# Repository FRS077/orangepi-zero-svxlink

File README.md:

# Shield OrangePi zero SvxLink

The purpose of this PCB is to easily interface one or two radio transceivers with an Orange Pi Zero. This makes it easy to create a simplex or duplex SvxLink access point.

It is assembled on top of the Orange Pi Zero and connected to the radios by two mini DIN connectors.

## Built With

- KiCad v7 - _Open Source CAD software_
- KiCad v7 Librairies - _Symbols, footprints and 3D models librairies_
- LCSC - _Electronic parts provider_ & JLCPCB - _Board manufacturing_

## Specifications

### Mini DIN Pinout

| No Pin | Simplex / Duplex RX | Duplex TX |
| :----: | :-----------------: | :-------: |
|   1    |      Audio Out      | Audio Out |
|   2    |       Ground        |  Ground   |
|   3    |         PTT         |    PTT    |
|   4    |   Audio In (9600)   |   _N/C_   |
|   5    |   Audio In (1200)   |   _N/C_   |
|   6    |       Squelch       |   _N/C_   |

PTT is connected on the Orange Pi Zero to PA07 and Squelch to PA10.

### Solder bridge selectors

| Name  | Usage                                     |         Choice A          |   Choice B    |
| :---: | :---------------------------------------- | :-----------------------: | :-----------: |
|  JP1  | Select the audio input                    | Audio In 1200 _(default)_ | Audio In 9600 |
|  JP2  | Select simplex/duplex mode (audio output) |        Duplex mode        |  Simplex mode |
|  JP3  | Select simplex/duplex mode (PTT)          |        Duplex mode        |  Simplex mode |

## Authors

- **Quentin Rahms** - _Intial work_
- **Alexis Moyart** - _Completion_

## License

This project is licensed under the MIT License - see the LICENSE.md file for details

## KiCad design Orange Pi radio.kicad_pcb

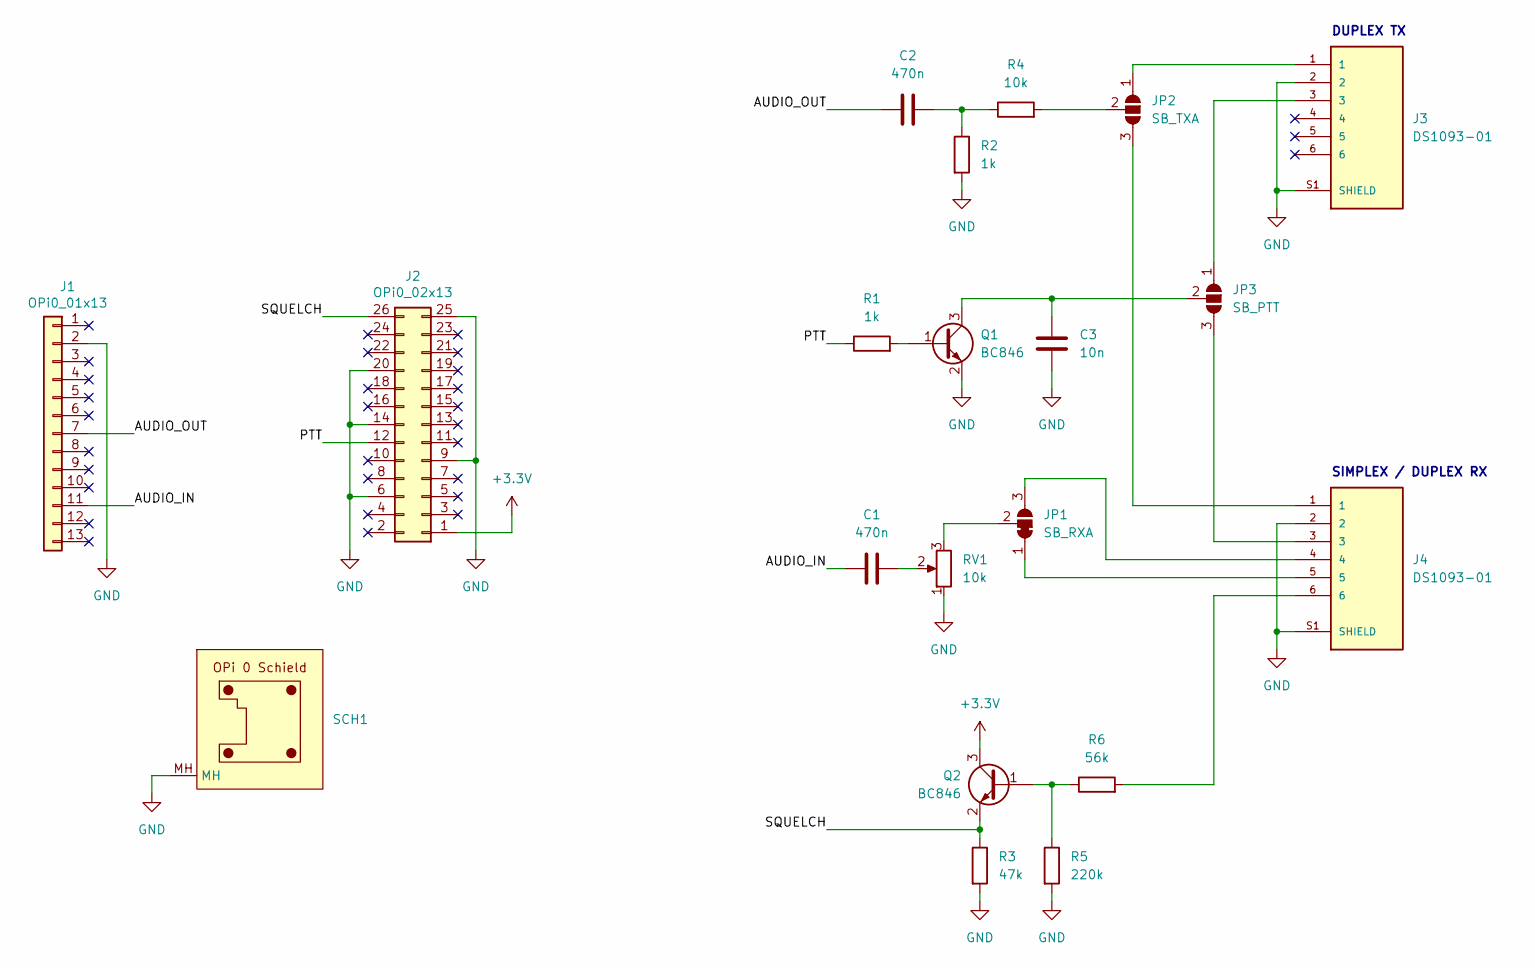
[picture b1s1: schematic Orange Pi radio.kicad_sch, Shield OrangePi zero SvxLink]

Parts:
C1, C2: 470n; C_0603_1608Metric_Pad1.08x0.95mm_HandSolder
C3: 10n; C_0603_1608Metric_Pad1.08x0.95mm_HandSolder
J1: OPi0_01x13; PinSocket_1x13_P2.54mm_Vertical
J2: OPi0_02x13; PinSocket_2x13_P2.54mm_Vertical
J3, J4: DS1093-01
JP1: SB_RXA; SolderJumper-3_P1.3mm_Bridged12_RoundedPad1.0x1.5mm
JP2: SB_TXA; SolderJumper-3_P1.3mm_Open_RoundedPad1.0x1.5mm
JP3: SB_PTT; SolderJumper-3_P1.3mm_Open_RoundedPad1.0x1.5mm
Q1, Q2: BC846; SOT-23
R1, R2: 1k; R_0603_1608Metric_Pad0.98x0.95mm_HandSolder
R3: 47k; R_0603_1608Metric_Pad0.98x0.95mm_HandSolder
R4: 10k; R_0603_1608Metric_Pad0.98x0.95mm_HandSolder
R5: 220k; R_0603_1608Metric_Pad0.98x0.95mm_HandSolder
R6: 56k; R_0603_1608Metric_Pad0.98x0.95mm_HandSolder
RV1: 10k; Potentiometer_Bourns_3314G_Vertical
SCH1: OPi0_schield

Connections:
+3.3V: J2.1, Q2.3 (C)
/AUDIO_IN: C1.1, J1.11
/AUDIO_OUT: C2.1, J1.7
/PTT: J2.12, R1.1
/SQUELCH: J2.26, Q2.2 (E), R3.1
GND: C3.2, J1.2, J2.6, J2.9, J2.14, J2.20, J2.25, J3.2, J3.S1 (SHIELD), J3.S2 (SHIELD), J3.S3 (SHIELD), J4.2, J4.S1 (SHIELD), J4.S2 (SHIELD), J4.S3 (SHIELD), Q1.2 (E), R2.2, R3.2, R5.2, RV1.1, SCH1.MH
unnamed: C1.2, RV1.2
unnamed: C2.2, R2.1, R4.1
unnamed: J4.6, R6.2
unnamed: J4.5, JP1.1 (A)
unnamed: J4.4, JP1.3 (B)
unnamed: JP1.2 (C), RV1.3
unnamed: J3.1, JP2.1 (A)
unnamed: J4.1, JP2.3 (B)
unnamed: JP2.2 (C), R4.2
unnamed: J3.3, JP3.1 (A)
unnamed: J4.3, JP3.3 (B)
unnamed: C3.1, JP3.2 (C), Q1.3 (C)
unnamed: Q1.1 (B), R1.2
unnamed: Q2.1 (B), R5.1, R6.1

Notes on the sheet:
SIMPLEX / DUPLEX RX
DUPLEX TX

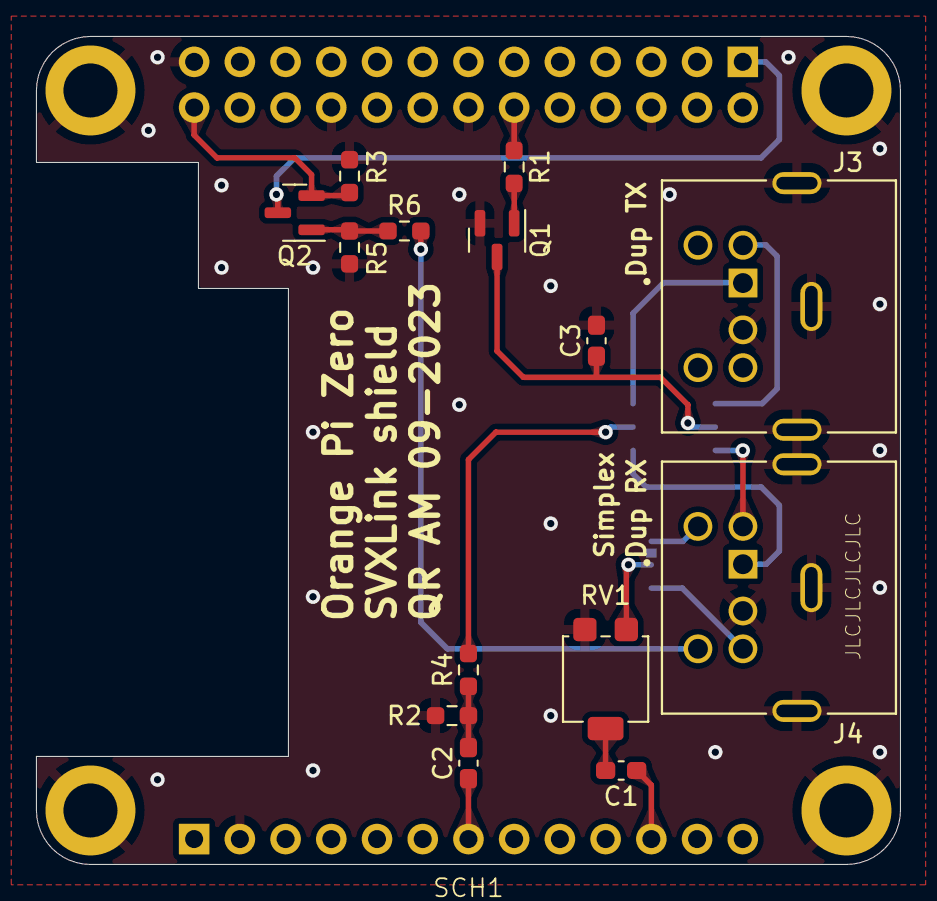
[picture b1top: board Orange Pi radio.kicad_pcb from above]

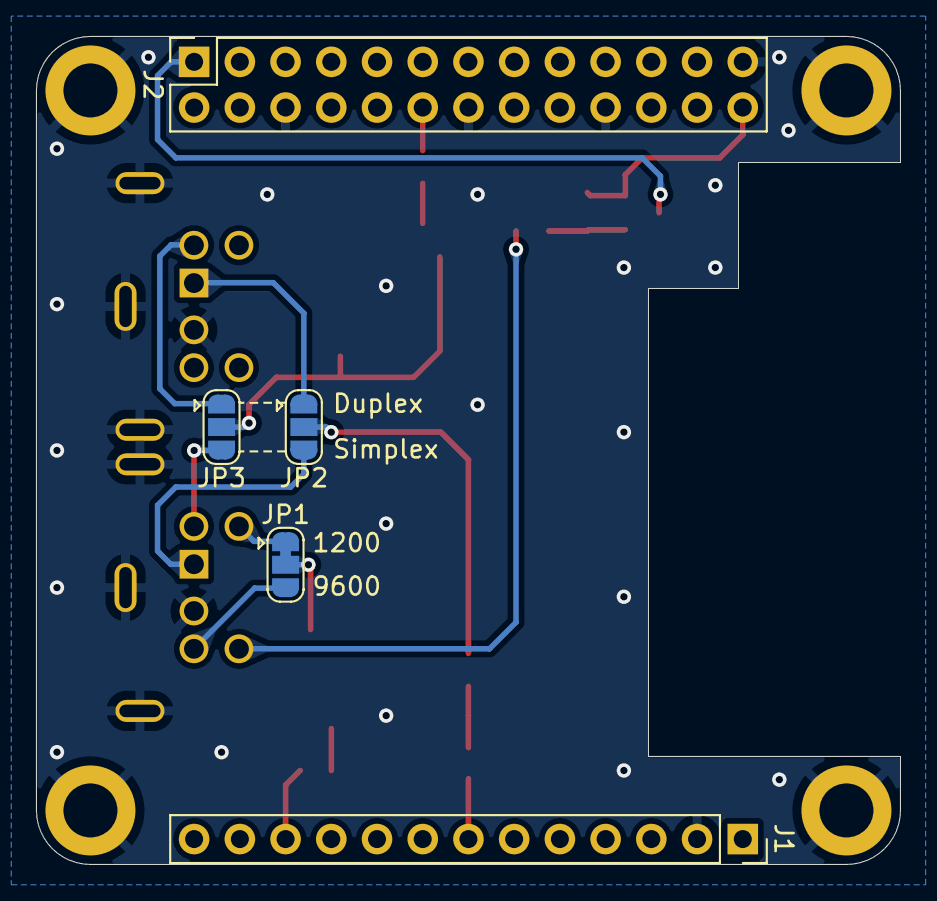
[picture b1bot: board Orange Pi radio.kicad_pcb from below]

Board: 2 copper layers, 48.0 x 46.0 mm, 20 parts (5 on the bottom side), 20 nets.

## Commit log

2025-07-20 FRS077
